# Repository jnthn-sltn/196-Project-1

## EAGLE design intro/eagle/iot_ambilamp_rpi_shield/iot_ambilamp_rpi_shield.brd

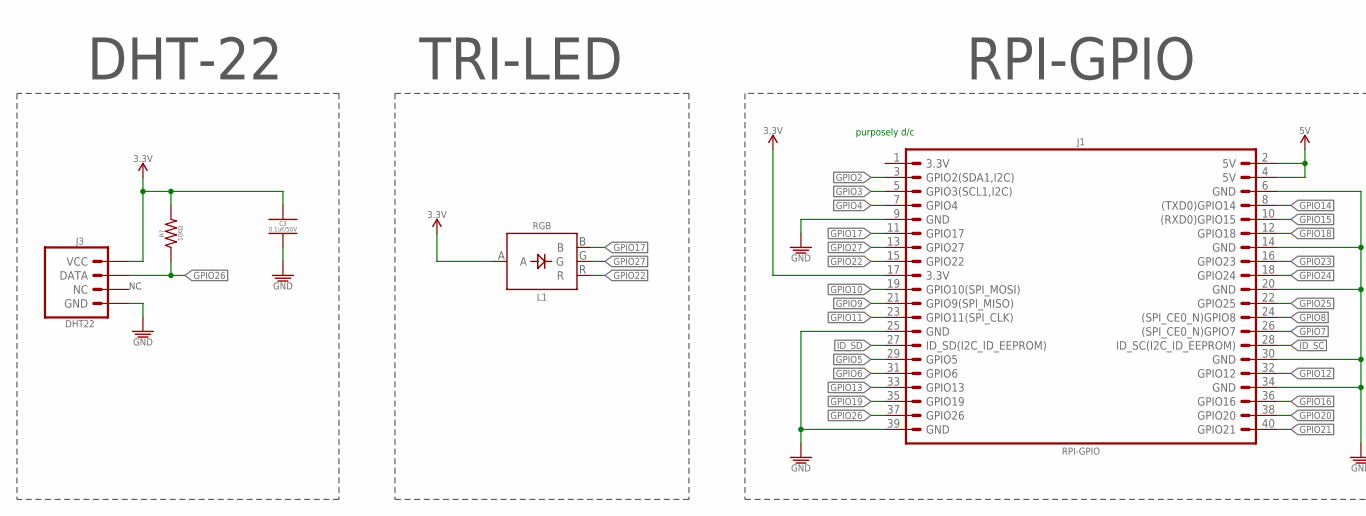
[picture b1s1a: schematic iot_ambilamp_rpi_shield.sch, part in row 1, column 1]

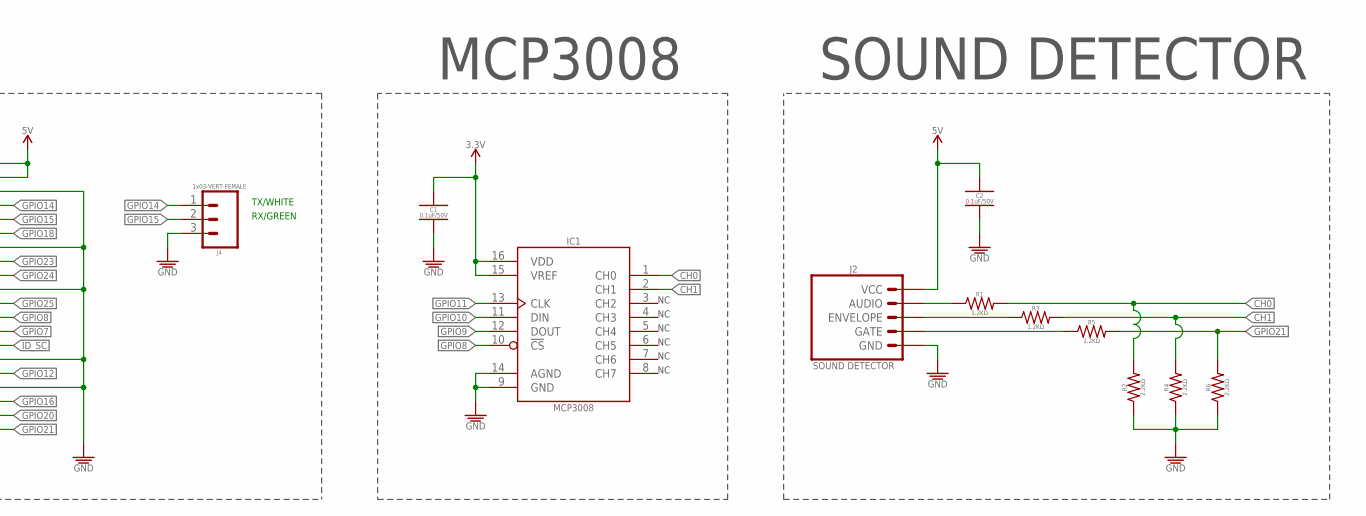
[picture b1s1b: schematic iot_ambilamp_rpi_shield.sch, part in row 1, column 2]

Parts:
C1, C2, C3: 0.1uF/50V; _CER_SMD-805
IC1: MCP3008; SO-16
J1: RPI-GPIO; RPI-GPIO_CONNECTOR_TALL
J2: SOUND DETECTOR; CONNECTOR-RA_SOUND-DETECTOR_SPARKFUN
J3: DHT22; CONNECTOR_TEMPERATURE-SENSOR_DHT22
J4: 1x03-VERT-FEMALE; 1X03-VERT-FEMALE
L1: RGB; LED-5MM-PTH_RGB-CA
R1, R3, R5: 1.2KΩ; RESISTOR_SMD-805
R2, R4, R6: 2.2KΩ; RESISTOR_SMD-805
R7: 10KΩ; RESISTOR_SMD-805

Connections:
3.3V: C1.1, C3.1, IC1.15 (VREF), IC1.16 (VDD), J1.17 (3.3V), J3.VCC, L1.A, R7.2
5V: C2.1, J1.2 (5V), J1.4 (5V), J2.VCC
CH0: IC1.1 (CH0), R1.2, R2.2
CH1: IC1.2 (CH1), R3.2, R4.2
GND: C1.2, C2.2, C3.2, IC1.9 (GND), IC1.14 (AGND), J1.6 (GND), J1.9 (GND), J1.14 (GND), J1.20 (GND), J1.25 (GND), J1.30 (GND), J1.34 (GND), J1.39 (GND), J2.GND, J3.GND, J4.3, R2.1, R4.1, R6.1
GPIO2: J1.3 (GPIO2(SDA1,I2C))
GPIO3: J1.5 (GPIO3(SCL1,I2C))
GPIO4: J1.7 (GPIO4)
GPIO5: J1.29 (GPIO5)
GPIO6: J1.31 (GPIO6)
GPIO7: J1.26 ((SPI_CE0_N)GPIO7)
GPIO8: IC1.10 (!CS), J1.24 ((SPI_CE0_N)GPIO8)
GPIO9: IC1.12 (DOUT), J1.21 (GPIO9(SPI_MISO))
GPIO10: IC1.11 (DIN), J1.19 (GPIO10(SPI_MOSI))
GPIO11: IC1.13 (CLK), J1.23 (GPIO11(SPI_CLK))
GPIO12: J1.32 (GPIO12)
GPIO13: J1.33 (GPIO13)
GPIO14: J1.8 ((TXD0)GPIO14), J4.1
GPIO15: J1.10 ((RXD0)GPIO15), J4.2
GPIO16: J1.36 (GPIO16)
GPIO17: J1.11 (GPIO17), L1.B
GPIO18: J1.12 (GPIO18)
GPIO19: J1.35 (GPIO19)
GPIO20: J1.38 (GPIO20)
GPIO21: J1.40 (GPIO21), R5.2, R6.2
GPIO22: J1.15 (GPIO22), L1.R
GPIO23: J1.16 (GPIO23)
GPIO24: J1.18 (GPIO24)
GPIO25: J1.22 (GPIO25)
GPIO26: J1.37 (GPIO26), J3.DATA, R7.1
GPIO27: J1.13 (GPIO27), L1.G
ID_SC: J1.28 (ID_SC(I2C_ID_EEPROM))
ID_SD: J1.27 (ID_SD(I2C_ID_EEPROM))
unnamed: J2.GATE, R5.1
unnamed: J2.ENVELOPE, R3.1
unnamed: J2.AUDIO, R1.1

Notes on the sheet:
MCP3008
RPI-GPIO
TRI-LED
SOUND DETECTOR
DHT-22
purposely d/c
TX/WHITE
RX/GREEN

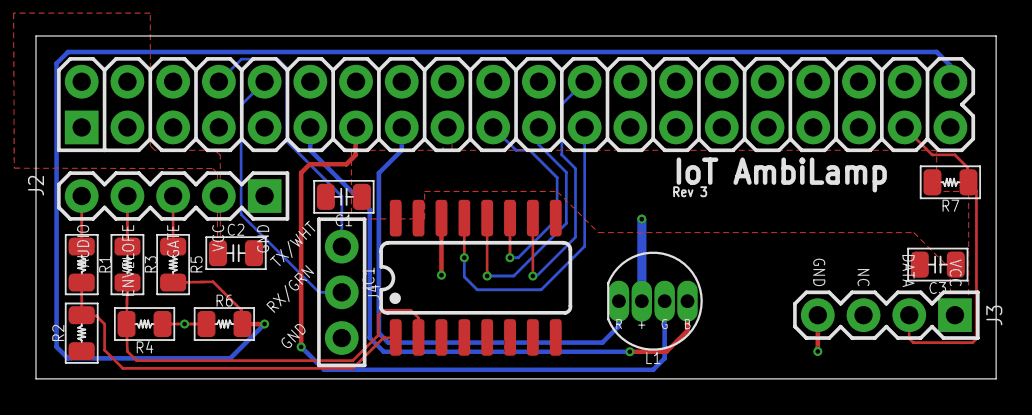
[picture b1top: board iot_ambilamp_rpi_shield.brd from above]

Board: 2 copper layers, 53.3 x 19.0 mm, 16 parts (0 on the bottom side), 19 nets.

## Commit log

2018-01-19 init with boilerplate html
2018-01-19 Included new files for webserver
2018-01-20 Completed webserver
2018-01-20 minor correction of Completed Project
2018-01-26 Changed from html to PHP
2018-01-26 removed redundant links
2018-01-26 Moved assets into assets folder
2018-01-26 updated links to assets folder
2018-01-26 updated links to assets folder2
2018-01-26 added new folder intro_to_iot_ambilamp
2018-01-26 added memory with php
2018-01-26 added memory with php2
2018-01-26 added memory with php3
2018-01-26 added memory with php4
2018-01-26 added memory with php5
2018-01-26 added line at top
2018-01-26 added at line20 index.php
2018-01-28 Added servocode
2018-01-28 Restructured Files
2018-01-28 file restructuring again
2018-01-28 file restructuring again2
2018-01-28 file restructuring again3
2018-01-28 servod edited
2018-01-28 restruct
2018-01-28 addedsuperscript file
2018-01-28 added sensors folder
2018-01-28 created python file
2018-01-28 corrected while loop
2018-01-28 corrected while loop2
2018-01-28 added sound sensor lib
2018-01-28 addedpython for sound sensor
2018-01-28 addedpython for sound sensor2
2018-01-28 addedpython for sound sensor3
2018-01-29 addedpython for sound sensor4
2018-02-05 added sensor pycs
2018-02-05 added db access through header.php and update to tempchart
2018-02-05 added db access through header.php and update to tempchart1.1
2018-02-05 added db access through header.php and update to tempchart1.2
2018-02-05 added db access through header.php and update to tempchart1.3
2018-02-05 added db access through header.php and update to tempchart1.34
2018-02-05 added db access through header.php and update to tempchart1.4
2018-02-05 added db access through header.php and update to tempchart1.5
2018-02-05 added db access through header.php and update to tempchart1.6
2018-02-05 added db access through header.php and update to tempchart1.7
2018-02-05 updated sound chart 1
2018-02-05 updated sound chart 1.1
2018-02-05 updated sound chart 1.2
2018-02-05 updated tables
2018-02-05 updated tables 1.1
2018-02-05 updated dbase for color
2018-02-05 updated dbase for color 1.1
2018-02-05 updated radar chart
2018-02-05 updated radar chart 1.1
2018-02-05 updated radar chart 1.2
2018-02-05 updated radar chart 1.3
2018-02-05 updated radar chart 1.4
2018-02-05 updated radar chart 1.5
2018-02-05 updated radar chart 1.6
2018-02-05 updated radar chart 1.7
2018-03-14 added image painter
